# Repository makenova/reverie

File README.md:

# Reverie

The reverie is a hot swap mini 1800 inspired by the [Elongate](https://geekhack.org/index.php?topic=106527), [Clarabelle](https://geekhack.org/index.php?topic=106380.0), and [Garbage Truck](https://www.reddit.com/r/MechanicalKeyboards/comments/gkb4nt/the_garbage_truck/) keyboards.
I made this because hot swap is usually left out in smaller runs of high end coustoms.

The plate file can be found in the [docs](./docs) folder.

## Wiring Guide

The following diagram displays the colums and rows.

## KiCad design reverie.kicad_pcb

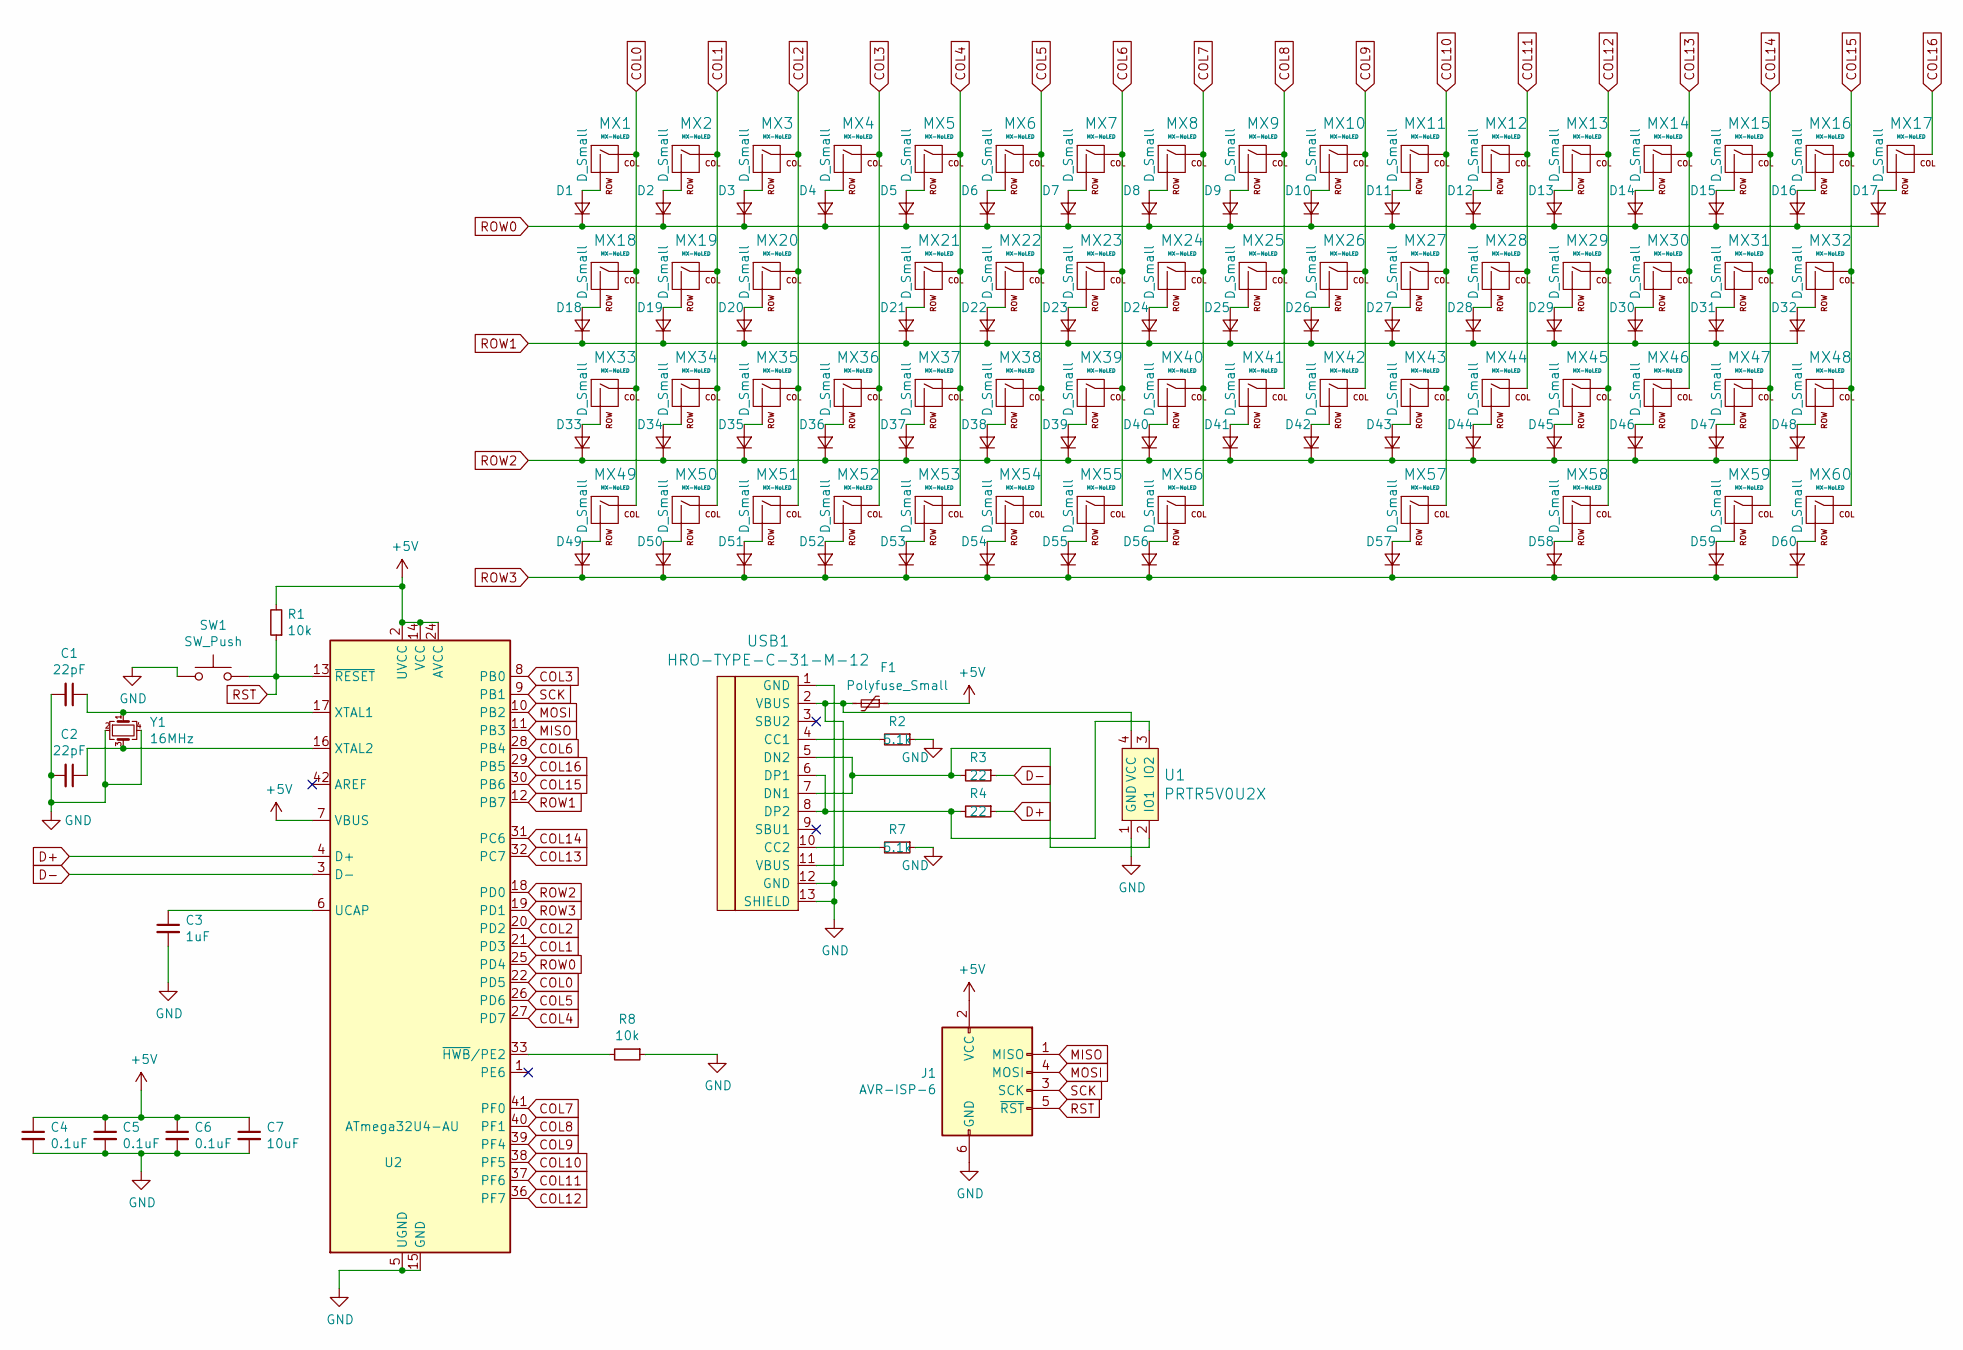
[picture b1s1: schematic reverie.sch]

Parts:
C1, C2: 22pF; C_0805_2012Metric
C3: 1uF; C_0805_2012Metric
C4, C5, C6: 0.1uF; C_0805_2012Metric
C7: 10uF; C_0805_2012Metric
D1, D2, D3, D4, D5, D6, D7, D8, D9, D10, D11, D12, D13, D14, D15, D16, D17, D18, D19, D20, D21, D22, D23, D24, D25, D26, D27, D28, D29, D30, D31, D32, D33, D34, D35, D36, D37, D38, D39, D40, D41, D42, D43, D44, D45, D46, D47, D48, D49, D50, D51, D52, D53, D54, D55, D56, D57, D58, D59, D60: D_Small; D_SOD-123
F1: Polyfuse_Small; Fuse_1206_3216Metric
J1: AVR-ISP-6; IDC-Header_2x03_P2.54mm_Vertical
MX1, MX2, MX3, MX4, MX5, MX6, MX7, MX8, MX9, MX10, MX11, MX12, MX13, MX14, MX15, MX16, MX17, MX18, MX19, MX20, MX22, MX23, MX24, MX25, MX26, MX27, MX28, MX29, MX30, MX31, MX33, MX34, MX35, MX36, MX38, MX39, MX40, MX41, MX42, MX43, MX44, MX45, MX46, MX47, MX49, MX50, MX51, MX52, MX53: MX-NoLED; MXOnly-1U-Hotswap
MX21, MX48, MX59, MX60: MX-NoLED; MXOnly-1.25U-Hotswap
MX32, MX37: MX-NoLED; MXOnly-1.75U-Hotswap
MX54, MX55, MX58: MX-NoLED; MXOnly-1.5U-Hotswap
MX56: MX-NoLED; MXOnly-2.25U-Hotswap-ReversedStabilizers
MX57: MX-NoLED; MXOnly-2.75U-Hotswap-ReversedStabilizers
R1, R8: 10k; R_0805_2012Metric
R2, R7: 5.1k; R_0805_2012Metric
R3, R4: 22; R_0805_2012Metric
SW1: SW_Push; SKQG-1155865
U1: PRTR5V0U2X; SOT143B
U2: ATmega32U4-AU; TQFP-44_10x10mm_P0.8mm
USB1: HRO-TYPE-C-31-M-12; HRO-TYPE-C-31-M-12-HandSoldering
Y1: 16MHz; Crystal_SMD_3225-4Pin_3.2x2.5mm

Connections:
+5V: C4.1, C5.1, C6.1, C7.1, F1.1, J1.2 (VCC), R1.2, U2.2 (UVCC), U2.7 (VBUS), U2.14 (VCC), U2.24 (AVCC), U2.34 (VCC), U2.44 (AVCC)
COL0: MX1.1 (COL), MX18.1 (COL), MX33.1 (COL), MX49.1 (COL), U2.22 (PD5)
COL1: MX2.1 (COL), MX19.1 (COL), MX34.1 (COL), MX50.1 (COL), U2.21 (PD3)
COL2: MX3.1 (COL), MX20.1 (COL), MX35.1 (COL), MX51.1 (COL), U2.20 (PD2)
COL3: MX4.1 (COL), MX36.1 (COL), MX52.1 (COL), U2.8 (PB0)
COL4: MX5.1 (COL), MX21.1 (COL), MX37.1 (COL), MX53.1 (COL), U2.27 (PD7)
COL5: MX6.1 (COL), MX22.1 (COL), MX38.1 (COL), MX54.1 (COL), U2.26 (PD6)
COL6: MX7.1 (COL), MX23.1 (COL), MX39.1 (COL), MX55.1 (COL), U2.28 (PB4)
COL7: MX8.1 (COL), MX24.1 (COL), MX40.1 (COL), MX56.1 (COL), U2.41 (PF0)
COL8: MX9.1 (COL), MX25.1 (COL), MX41.1 (COL), U2.40 (PF1)
COL9: MX10.1 (COL), MX26.1 (COL), MX42.1 (COL), U2.39 (PF4)
COL10: MX11.1 (COL), MX27.1 (COL), MX43.1 (COL), MX57.1 (COL), U2.38 (PF5)
COL11: MX12.1 (COL), MX28.1 (COL), MX44.1 (COL), U2.37 (PF6)
COL12: MX13.1 (COL), MX29.1 (COL), MX45.1 (COL), MX58.1 (COL), U2.36 (PF7)
COL13: MX14.1 (COL), MX30.1 (COL), MX46.1 (COL), U2.32 (PC7)
COL14: MX15.1 (COL), MX31.1 (COL), MX47.1 (COL), MX59.1 (COL), U2.31 (PC6)
COL15: MX16.1 (COL), MX32.1 (COL), MX48.1 (COL), MX60.1 (COL), U2.30 (PB6)
COL16: MX17.1 (COL), U2.29 (PB5)
D+: R4.1, U2.4 (D+)
D-: R3.1, U2.3 (D-)
GND: C1.2, C2.2, C3.2, C4.2, C5.2, C6.2, C7.2, J1.6 (GND), R2.1, R7.1, R8.1, SW1.1, U1.1 (GND), U2.5 (UGND), U2.15 (GND), U2.23 (GND), U2.35 (GND), U2.43 (GND), USB1.1 (GND), USB1.12 (GND), USB1.13 (SHIELD), Y1.2, Y1.4
MISO: J1.1 (MISO), U2.11 (PB3)
MOSI: J1.4 (MOSI), U2.10 (PB2)
unnamed: C1.1, U2.17 (XTAL1), Y1.1
unnamed: C2.1, U2.16 (XTAL2), Y1.3
unnamed: C3.1, U2.6 (UCAP)
unnamed: D1.2 (A), MX1.2 (ROW)
unnamed: D2.2 (A), MX2.2 (ROW)
unnamed: D3.2 (A), MX3.2 (ROW)
unnamed: D4.2 (A), MX4.2 (ROW)
unnamed: D5.2 (A), MX5.2 (ROW)
unnamed: D6.2 (A), MX6.2 (ROW)
unnamed: D7.2 (A), MX7.2 (ROW)
unnamed: D8.2 (A), MX8.2 (ROW)
unnamed: D9.2 (A), MX9.2 (ROW)
unnamed: D10.2 (A), MX10.2 (ROW)
unnamed: D11.2 (A), MX11.2 (ROW)
unnamed: D12.2 (A), MX12.2 (ROW)
unnamed: D13.2 (A), MX13.2 (ROW)
unnamed: D14.2 (A), MX14.2 (ROW)
unnamed: D15.2 (A), MX15.2 (ROW)
unnamed: D16.2 (A), MX16.2 (ROW)
unnamed: D17.2 (A), MX17.2 (ROW)
unnamed: D18.2 (A), MX18.2 (ROW)
unnamed: D19.2 (A), MX19.2 (ROW)
unnamed: D20.2 (A), MX20.2 (ROW)
unnamed: D21.2 (A), MX21.2 (ROW)
unnamed: D22.2 (A), MX22.2 (ROW)
unnamed: D23.2 (A), MX23.2 (ROW)
unnamed: D24.2 (A), MX24.2 (ROW)
unnamed: D25.2 (A), MX25.2 (ROW)
unnamed: D26.2 (A), MX26.2 (ROW)
unnamed: D27.2 (A), MX27.2 (ROW)
unnamed: D28.2 (A), MX28.2 (ROW)
unnamed: D29.2 (A), MX29.2 (ROW)
unnamed: D30.2 (A), MX30.2 (ROW)
unnamed: D31.2 (A), MX31.2 (ROW)
unnamed: D32.2 (A), MX32.2 (ROW)
unnamed: D33.2 (A), MX33.2 (ROW)
unnamed: D34.2 (A), MX34.2 (ROW)
unnamed: D35.2 (A), MX35.2 (ROW)
unnamed: D36.2 (A), MX36.2 (ROW)
unnamed: D37.2 (A), MX37.2 (ROW)
unnamed: D38.2 (A), MX38.2 (ROW)
unnamed: D39.2 (A), MX39.2 (ROW)
unnamed: D40.2 (A), MX40.2 (ROW)
unnamed: D41.2 (A), MX41.2 (ROW)
unnamed: D42.2 (A), MX42.2 (ROW)
unnamed: D43.2 (A), MX43.2 (ROW)
unnamed: D44.2 (A), MX44.2 (ROW)
unnamed: D45.2 (A), MX45.2 (ROW)
unnamed: D46.2 (A), MX46.2 (ROW)
unnamed: D47.2 (A), MX47.2 (ROW)
unnamed: D48.2 (A), MX48.2 (ROW)
unnamed: D49.2 (A), MX49.2 (ROW)
unnamed: D50.2 (A), MX50.2 (ROW)
unnamed: D51.2 (A), MX51.2 (ROW)
unnamed: D52.2 (A), MX52.2 (ROW)
unnamed: D53.2 (A), MX53.2 (ROW)
unnamed: D54.2 (A), MX54.2 (ROW)
unnamed: D55.2 (A), MX55.2 (ROW)
unnamed: D56.2 (A), MX56.2 (ROW)
unnamed: D57.2 (A), MX57.2 (ROW)
unnamed: D58.2 (A), MX58.2 (ROW)
unnamed: D59.2 (A), MX59.2 (ROW)
unnamed: D60.2 (A), MX60.2 (ROW)
unnamed: F1.2, U1.4 (VCC), USB1.2 (VBUS), USB1.11 (VBUS)
unnamed: R2.2, USB1.4 (CC1)
unnamed: R3.2, U1.2 (IO1), USB1.5 (DN2), USB1.7 (DN1)
unnamed: R4.2, U1.3 (IO2), USB1.6 (DP1), USB1.8 (DP2)
unnamed: R7.2, USB1.10 (CC2)
unnamed: R8.2, U2.33 (~HWB~/PE2)
ROW0: D1.1 (K), D2.1 (K), D3.1 (K), D4.1 (K), D5.1 (K), D6.1 (K), D7.1 (K), D8.1 (K), D9.1 (K), D10.1 (K), D11.1 (K), D12.1 (K), D13.1 (K), D14.1 (K), D15.1 (K), D16.1 (K), D17.1 (K), U2.25 (PD4)
ROW1: D18.1 (K), D19.1 (K), D20.1 (K), D21.1 (K), D22.1 (K), D23.1 (K), D24.1 (K), D25.1 (K), D26.1 (K), D27.1 (K), D28.1 (K), D29.1 (K), D30.1 (K), D31.1 (K), D32.1 (K), U2.12 (PB7)
ROW2: D33.1 (K), D34.1 (K), D35.1 (K), D36.1 (K), D37.1 (K), D38.1 (K), D39.1 (K), D40.1 (K), D41.1 (K), D42.1 (K), D43.1 (K), D44.1 (K), D45.1 (K), D46.1 (K), D47.1 (K), D48.1 (K), U2.18 (PD0)
ROW3: D49.1 (K), D50.1 (K), D51.1 (K), D52.1 (K), D53.1 (K), D54.1 (K), D55.1 (K), D56.1 (K), D57.1 (K), D58.1 (K), D59.1 (K), D60.1 (K), U2.19 (PD1)
RST: J1.5 (~RST), R1.1, SW1.2, U2.13 (~RESET)
SCK: J1.3 (SCK), U2.9 (PB1)

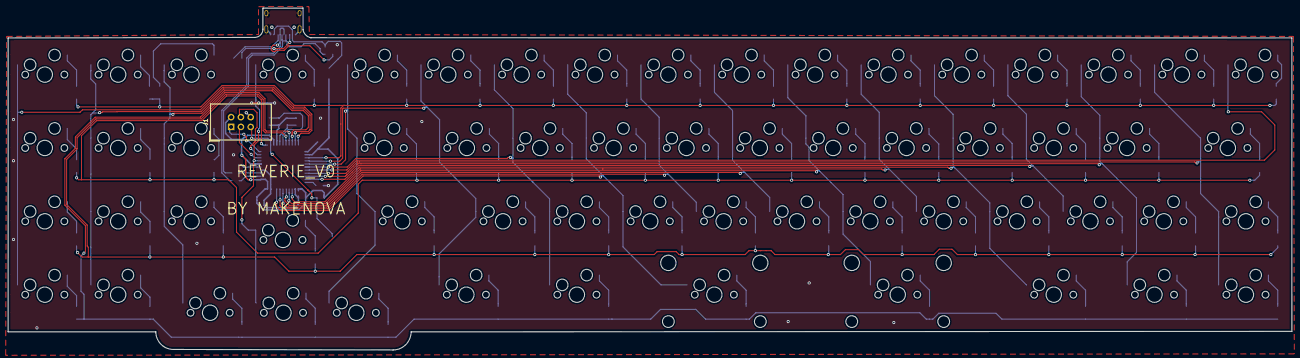
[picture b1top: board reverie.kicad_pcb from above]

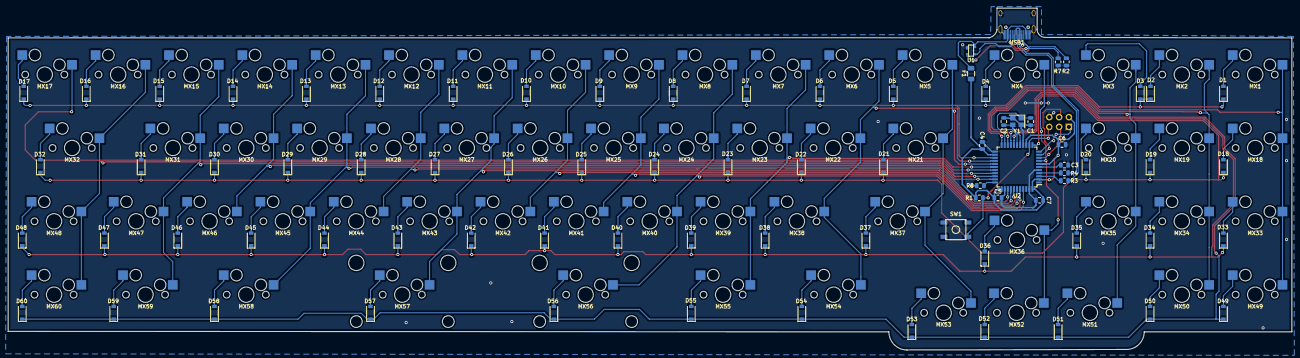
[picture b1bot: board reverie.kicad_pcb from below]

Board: 2 copper layers, 333.4 x 88.8 mm, 140 parts (79 on the bottom side), 98 nets.

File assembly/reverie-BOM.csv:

"Designator","Quantity","Value","Footprint","LCSC Part #"
"C1, C2, ","2","22pF","0805","C1804"
"C3, ","1","1uF","0805","C28323"
"C4, C5, C6, ","3","0.1uF","0805","C49678"
"C7, ","1","10uF","0805","C15850"
"D1, D2, D3, D4, D5, D6, D7, D8, D9, D10, D11, D12, D13, D14, D15, D16, D17, D18, D19, D20, D21, D22, D23, D24, D25, D26, D27, D28, D29, D30, D31, D32, D33, D34, D35, D37, D38, D39, D40, D41, D42, D43, D44, D45, D46, D47, D48, D36, D49, D50, D51, D53, D54, D55, D56, D57, D58, D59, D60, D52, ","60","D_Small","SOD-123","C81598"
"F1, ","1","Polyfuse_Small","1206","C151162"
"R2, R7, ","2","5.1k","0805","C27834"
"R3, R4, ","2","22","0805","C17561"
"R8, R1, ","2","10k","0805","C17414"
"SW1, ","1","SW_Push",":SMD-SW-4_5.1x5.1x1.5","C318884"
"U1, ","1","PRTR5V0U2X",":SOT-143","C78442"
"U2, ","1","ATmega32U4-AU","QFP-44_10.0x10.0x0.8P","C44854"
"Y1, ","1","16MHz","SMD-3225_4P","C13738"

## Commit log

2020-05-18 make it so
    add libraries and footprints to schematic and pcb in project specific libraries
2020-05-18 wire up the mcu
2020-05-19 update schematic
    add swtich matrix, usb, and esd circuits
    assign footprints
2020-05-19 add readme
    add KLE diagram
    add wiring guide diagram
    add plate file
2020-05-19 align diodes on pcb
2020-05-21 initial layout and routing
2020-05-24 complete routing
    add ISP programmer
2020-05-24 clean up
2020-05-24 add vanity silk text
2020-05-24 generate production files
    BOM
    Placement files
    gerbers
2020-05-24 add tracespace files
2020-05-24 add links to readme
2020-05-24 reshape edge cuts
    regenerate gerber drill files and tracespace
2020-06-02 work on edgecuts and replace isp footprint
2020-06-12 reverse stabilizers on plate
2020-06-15 case stuff
2020-06-20 export reverie plate
